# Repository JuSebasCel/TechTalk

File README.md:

# TechTalk
Un guante que, mediante la combinación de dedos, emite frases o palabras predefinidas en forma de sonido. También cuenta con una aplicación diseñada en Flutter que permite al usuario personalizar los perfiles y combinaciones del dispositivo, entre otras cosas.

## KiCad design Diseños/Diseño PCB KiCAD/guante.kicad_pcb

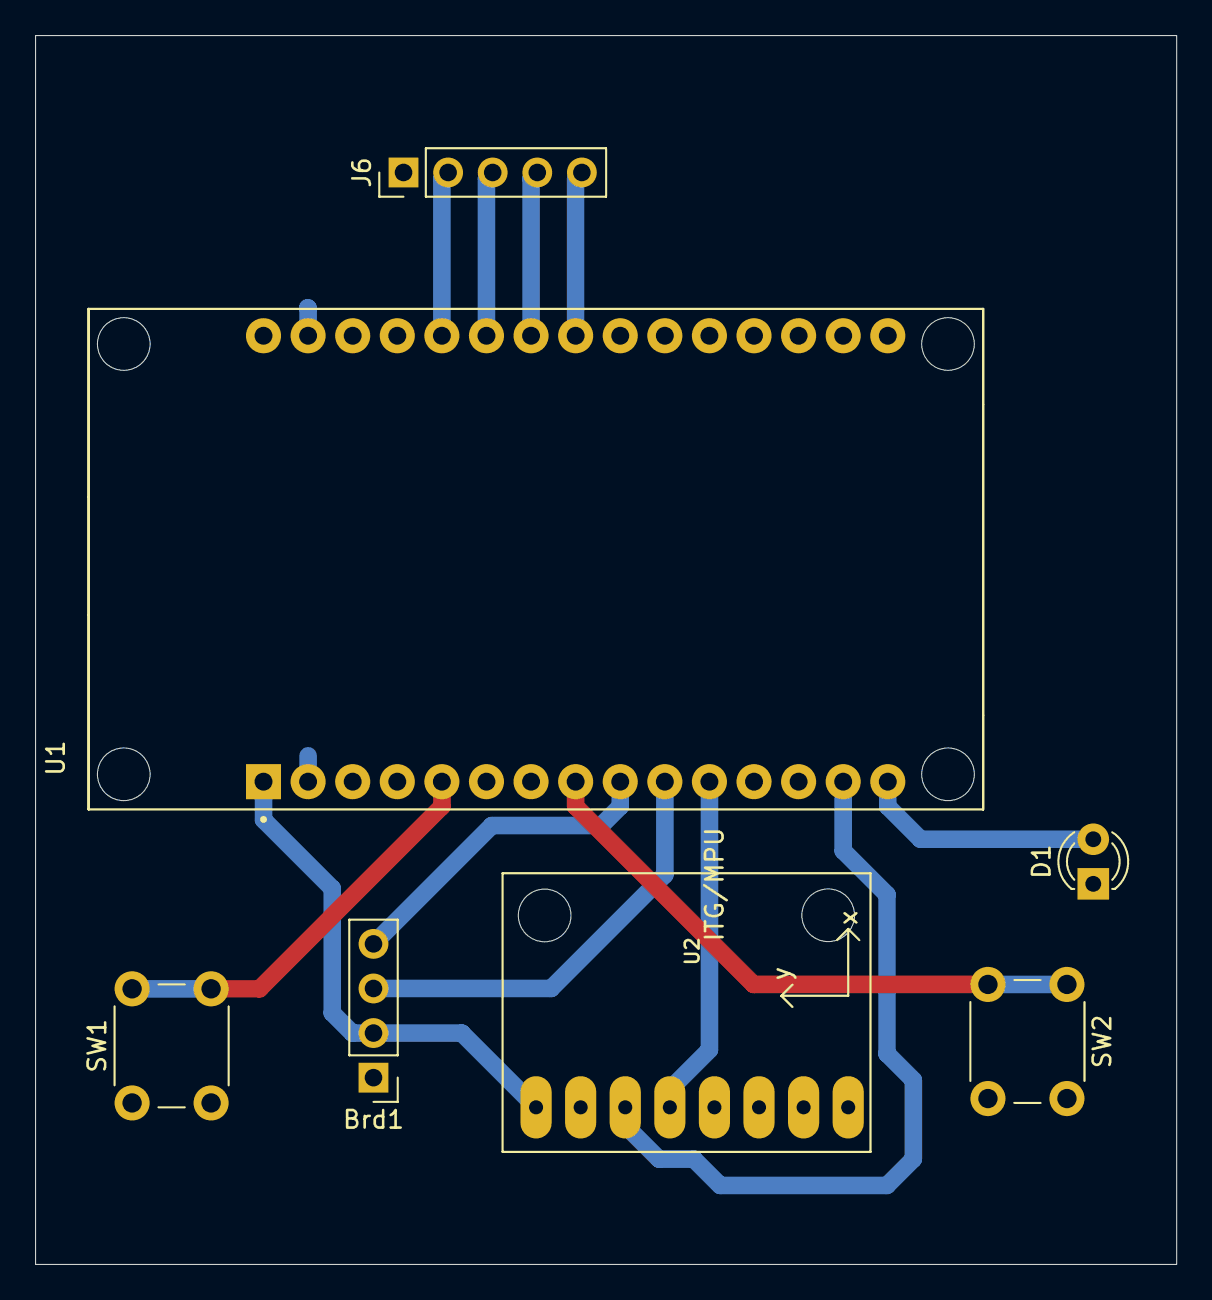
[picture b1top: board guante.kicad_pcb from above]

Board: 2 copper layers, 65.0 x 70.0 mm, 7 parts (0 on the bottom side), 13 nets.

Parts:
Brd1: SSD1306; PinHeader_1x04_P2.54mm_Vertical
D1: LED; LED_D3.0mm
J6: Conn_01x05_Pin; PinHeader_1x05_P2.54mm_Vertical
SW1, SW2: SW_Push; SW_PUSH_6mm
U1: ESP32-DEVKIT-V1; MODULE_ESP32_DEVKIT_V1
U2: GY-521

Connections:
unnamed: Brd1.1 (GND), D1.1 (K), J6.1, SW1.2, SW2.1, SW2.2, U1.2 (GND), U1.29 (GND), U2.GND
unnamed: Brd1.3 (SCL), U1.10 (D19)
unnamed: Brd1.4 (SDA), U1.9 (D18)
unnamed: Brd1.2 (VCC), U1.1 (3V3), U2.VCC
unnamed: D1.2 (A), U1.15 (D23)
unnamed: J6.2, U1.26 (D14)
unnamed: J6.3, U1.25 (D27)
unnamed: J6.4, U1.24 (D26)
unnamed: J6.5, U1.23 (D25)
unnamed: SW1.1 (2), U1.5 (D4)
unnamed: SW2.1 (2), U1.8 (D5)
unnamed: U1.11 (D21), U2.SDA
unnamed: U1.14 (D22), U2.SCL

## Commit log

2025-07-13 Estructura base del repositorio
    Se crean las carpetas necesarias para empezar a dar estructura de organización que requiere el proyecto.
2025-07-13 Versión 1 Código Microcontrolador
    El código reconoce las combinaciones de los dedos y muestra en el serial la frase asignada de manera manual en forma de if anidados, también funcionan botones para cambio de perfil y encendido/apagad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
2025-07-13 Versión 2 Código Microcontrolador
    El código ahora genera una conexión BLE permitiendo que se envie en forma de serial un archivo json, mismo que reescribe y guarde en una memoria de aproximadamente 3 a 4MB generada por SPIFFS
2025-07-13 Versión 3 Código Microcontrolador
    Se incluye la funcionalidad del giroscopio para aumentar las combinaciones de cada perfil, se implementa, cambia la clave del <map> añadiendo un carácter indicador de la posición, mismo definido por 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
2025-07-13 Versión 4 Código Microcontrolador
    El código ahora usa de manera directa el sensor MPU6050 para reconocer el eje Z permitiendo generar mas combinaciones por perfil.
2025-07-13 Versión 5 Código Microcontrolador
    Se implementa pantalla OLED para ello se generan dos conexiones de la librería Wire, para usar al mismo tiempo dos I2C, se añaden las funcionalidades para la pantalla además de una nueva funcionalida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
2025-07-13 App Personalizaciones
    Todo el directorio de la app, desde los assets, hasta screens, paquetes usados y demás, la aplicación actualmente funciona con SDK 27 y la API 35 (CompileSDK).
2025-07-14 Avances Raspberry Pi Zero W
    Codigos que se lograron desarrollar para probar y dimensionar la aplicabilidad de la raspberry pi, además de códigos necesarios para el funcionamiento de la misma, como lo son el wpa_supplicant.
2025-07-14 Generador de Sonido
    Diferentes opciones de generación de audio con librerías TTS buscando la que tenga mejor calidad.
2025-07-15 README Directorio OnShape
    Se crea el directorio donde se encuentran los registros de los avances relativos al diseño y esquema tanto del case como la pulsera.
2025-07-16 Códigos de Prueba Unitarios
    "Códigos que fueron usados principalmente para probar los componentes que se iban agregando al sistema, desde el giroscopio y sus acelerómetros, hasta la OLED y su capacidad de hacer una especie de e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
2025-07-18 Archivos fuente KiCAD
    Se suben los archivos de desarrollo de la PCB
2025-07-21 Cuerpo Pulsera
2025-07-21 Esquema Estuche
2025-07-24 Diagramas
    Se adjunta de extra los diagramas realizados durante taller que ya se encontraban previamente en la wiki del repositorio.
